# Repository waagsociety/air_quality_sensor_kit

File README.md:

# Air quality sensor kit
This repo contains documentation, source files and code for the following air quality sensor kits:

- Bora kit
- Bora Lora kit
- rIoT
- Responsive bird

### Bora kit
Air Quality Sensor for the Amsterdam Smart Citizens Lab, measures NO2, dust, temperature and humidity. Developed for a pilot in 2016 to measure air quality around the Valkenburgerstraat and Weesperstraat, under the name [Urban AirQ](http://waag.org/en/project/urban-airq). Citizens actively participated in the measuring process.

### Bora lora kit
The Bora kit was further developed during the [Smart Kids Lab](https://waag.org/en/blog/smart-citizen-kit-measuring-children-school) pilot to improve some criticalities with [LoraWAN](https://www.lora-alliance.org/What-IsLoRa/Technology):
- unstable and weak connectivity of the wifi module
- high power consumption,
- lack of real time data visualization.

### rIot
TBA

##### Credits
Partners: KNMI, University of Wageningen, GGD Amsterdam, ECN and the LongFonds. Waag Society earlier conducted a pilot with the Smart Citizen Kit in Amsterdam to measure air quality.

Partly financed by the Amsterdam Institute for Advanced Metropolitan Solutions (AMS). The project is also part of the European financed program Making Sense. This project has received funding from the European Union’s Horizon 2020 research and innovation programme under grant agreement no. 688620.

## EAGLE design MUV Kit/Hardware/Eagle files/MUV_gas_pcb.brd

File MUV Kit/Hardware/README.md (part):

If you are planning to produce the boards in the fablab you are in the right place. On this page you find instructions that will guide you during the process.
If you want to save time (and budget) you can download and use the gerber files of the customised boards from [folder](https://github.com/waagsociety/air_quality_sensor_kit/tree/master/MUV%20Kit/Hardware/Gerber%20files).

## Fab pcbs

The Fab boards are made using the small milling machine Roland Modela MDX-20, each pcbs requires at least two jobs: mill the trace and cut/drill the boards, in the folder digital files you find the png machinable files. When the pcb is double-side (the components and/or traces are on both side), the jobs are four: [double side milling](https://github.com/waagsociety/air_quality_sensor_kit/tree/master/MUV%20Kit/Hardware/Double%20side%20milling).

Tools used:
- one side and double side copper plate, FR1
- to mill the traces: endmill, 1/64inch diameter
- to cut and drill: endmill, 1/32inch diameter

In Fablab Amsterdam the software to generate the rml file and send it to the machine is Fabmodules. It is highly recommended to use the last version of Fabmodules, aka mods http://mods.cba.mit.edu/; previous versions of fabmodules, still work but double check the output of the software before to send the job to the machine, in some cases the path is not well calculated.

In the image below you find the setting to envrage the traces and to drill holes/cut the board.
<br>

Note: when you mill the outlines, you will need to trick the fabmodules!! Some holes are two smalls to be identified with a diameter tool of 1/64inch (0.79248mm) so you can set the diameter tool to 0.78mm and all the holes will be milled; yes, you lose some copper on the pad but it is still enough to solder vias and components.

#### Sensors pcb
| top view  | bottom view |
| ------------- | ------------- |
| |  |
| Components placed on the top layer  <br> but soldered on the bottom! <br>  <br> JP1: female THT 1x12 pin header, 2.54pitch <br> JP2: female THT 1x16 pin header 2.54pitch <br> J-GAS, J-DB. J-BME : Grove - Universal 4 Pin connector <br> 05-JST-B5B: Connector Wire-To-Board, B5B-XH-A (LF)(SN) <br> red traces: jumper wires between vias| Components placed on the bottom layer <br> and soldered on the bottom side <br>  <br> Q1/Q2 : BSS138 mosfet, also the NDS355AN from the fab inventory is ok. <br> R1/R2/R3/R4 : 10 Kohm <br> D1/D2 : diodes <br><br><br><br>|
|   | |

On the sensors pcb, it is not necessary to use all the connectors.
Depending on the sensors you want you use you can solder the required sockets. The J-GAS-NO1 and J-GAS-NO2 are dedicated to the Alphasense gas input devices. In this repo we are using only one sensor, the NO2 detector and it is connected to J-GAS-NO1.

#### Interface pcb
| top view  | bottom view |
| ------------- | ------------- |
|  | |
|Components placed on the top layer <br>   <br> SW_RST, SW_CONFIG: push button, smd, 6mm <br> LED1: WS2812B smd <br> R1: 10K res, smd, 1206 <br> R2: 470 ohm res, smd, 1206 <br> C1: 0.1uF cap, smd, 1206| Components placed on the bottom layer <br>  <br> JP3: female THT 1x12 pin header, 2.54pitch <br> JP1: female THT 1x16 pin header 2.54pitch <br><br><br><br>|

#### Temp/Hum pcb
| top view  | bottom view |
| ------------- | ------------- |
|   | |
| Components placed on the top layer <br>   <br> J3: female THT 1x6 pin header, 2.54pitch| Components placed on the bottom layer <br>  <br> J1: Grove - Universal 4 Pin connector|

The temp/hum pcb is a 2 layers board, the vias can be filled in with solid core wire (diameter < 0.8 mm). More information about the production of a double side pcb are in the [Double side milling](https://github.com/waagsociety/air_quality_sensor_kit/tree/master/MUV%20Kit/Hardware/Double%20side%20milling) section.

#### Gas pcb
| top view  | bottom view |
| ------------- | ------------- |
|   | |
| Components placed on the top layer <br>   <br> J2: Grove - Universal 4 Pin connector <br> JP1: female THT 1x10 pin header, 2.54pitch <br><br>| Components placed on the bottom layer <br>  <br> R1 or R2: 0 ohm resistor, smd, 1206 <br> C1: 100nF capacitor, smd, 1206 <br> C2: 1uF capacitor, smd, 1206 |

Note: this board can be used for both NO2 and O3 sensor but it is necessary to solder the zero ohm resistor in the different places depending on the gas. For the NO2 sensor the zero ohm resistor must be placed on R1, for the O3 sensor the zero ohm resistor must be placed on R2.

#### Noise pcb
| top view  | bottom view |
| ------------- | ------------- |
|   | |
| Components placed on the top layer <br>  <br> J1: Grove - Universal 4 Pin connector <br> OTS1_short: female THT 1x12 pin header, 2.54pitch <br> OTS1_long: female THT 1x16 pin header, 2.54pitch | There are no components placed on the bottom layer <br>  <br><br><br><br>|

## Off-the-shelf pcbs

#### Adafruit Feather esp8266
The [Adafruit Feather HUZZAH ESP8266](https://learn.adafruit.com/adafruit-feather-huzzah-esp8266?view=all) is an 'all-in-one' ESP8226 WiFi development board. The module can be supplied through USB cable with the following specifications:
* Measures 2.0" x 0.9" x 0.28" (51mm x 23mm x 8mm) without headers soldered in
* Light as a (large?) feather - 6 grams
* ESP8266 @ 80MHz or 160 Mhz with 3.3V logic/power
* 4MB of FLASH (32 Mbit)
* 3.3V regulator with 500mA peak current output
* CP2104 USB-Serial converter onboard with 921600 max baudrate for uploading
* Auto-reset support for getting into bootload mode before firmware upload
* 9 GPIO pins - can also be used as I2C and SPI
* 1 x analog inputs 1.0V max
* Pin #0 red LED for general purpose blinking. Pin #2 blue LED for bootloading debug & general purpose blinking
* Power/enable pin
* 4 mounting holes
* Reset button<br>

In this application the feather esp8266 is responsible to collect the measurements of the sensors and send them, via WiFi, to the dedicated server.
When the Wifi network is not available it can save the data on a SD-card, embedded on a different pcb, see section below.

The feather esp8266 requires female stacking headers so it can be plugged on the sensors pcb and it can host, on top, the RTC/SD-card pcb. The headers must be bought separately and they must be solder on the feather esp8266 board.

#### Adafruit Feather RTC and SD-card
The [Adalogger FeatherWing - RTC + SD](https://learn.adafruit.com/adafruit-adalogger-featherwing/overview) is compatible with the feather esp8266 and it features:
* an I2C real time clock (PCF8523) with 32KHz crystal and battery backup.
* microSD socket that connects to the SPI port pins. A CR1220 coin cell is required to use the RTC battery-backup capabilities.

As for the feather esp8266, it needs the female stacking headers that don't come with the board but they must be separately bought and soldered.

#### BME280 breakout board
The [bme280](https://www.bosch-sensortec.com/bst/products/all_products/bme280) sensor is so small (2.5x2.5 mm) that it is easier to work with its breakout board. The sensor works at 3.3V and it can communicate directly with the feather esp8266 that is also run at 3.3V, it means no need of level shifters between the two. Depending on where you buy the device, the board could already have the pin header, otherwise it is necessary to solder a 1x6 male header, 2.54mm pitch.

#### ADS1115 breakout board
The [ADS1115 board](https://learn.adafruit.com/adafruit-4-channel-adc-breakouts/) from Adafruit is the breakout board of the high-resolution Analog-to-Digital converter ADS1115. It is used in the reading of small voltages from the Gas sensors. The board can run from 2ßV up to 5V, in the kit it is supplied at 5V, same domain of the gas sensor, and it executes a two differential input readings.<br>
The [ADS1115](http://www.ti.com/lit/ds/symlink/ads1115.pdf) features:
* Resolution: 16 Bits
* Programmable Sample Rate: 8 to 860 Samples/Second
* Power Supply/Logic Levels: 2.0V to 5.5V
* Low Current Consumption: Continuous Mode: Only 150µA * Single-Shot Mode: Auto Shut-Down
* Internal Low-Drift Voltage Reference
* Internal Oscillator
* Internal PGA: up to x16
* I2C Interface: 4-Pin-Selectable Addresses
* Four Single-Ended or 2 Differential Inputs
* Programmable Comparator  

In the sensor kit, the ADS1115 board needs a 1x10 male pin header, pitch 2.54mm.

#### Adafruit Feather M0 Basic Proto
The Feather M0 Basic Proto has the ATSAMD21G18 ARM Cortex M0 processor as core, it clocked at 48MHz with 3,3V logic. Some specs:

* Measures 2.0" x 0.9" x 0.28" (51mm x 23mm x 8mm) without headers soldered in
* Light as a (large?) feather - 4.6 grams
* ATSAMD21G18 @ 48MHz with 3.3V logic/power
* 256KB of FLASH + 32KB of RAM
* 32.768 Khz crystal for clock generation & RTC
* 3.3V regulator with 500mA peak current output
* USB native support, comes with USB bootloader and * serial port debugging
* 20 GPIO pins
* Hardware Serial, hardware I2C, hardware SPI support
PWM outputs on all pins
* 6 x 12-bit analog inputs
* 1 x 10-bit analog output (DAC)
* Built in 100mA lipoly charger with charging status indicator LED, not in used in sensor kit.
* Pin #13 red LED for general purpose blinking
* Power/enable pin
* 4 mounting holes
* Reset button

In the kit the feather M0 is responsible to communicate with mic for the noise measurements and it sends the data to the feather esp8266 over serial.
The connect the fetaher M0 to pheripheral devices is necessary to solder:
* two 1x3 female pin headers on the proto part of the feather, as socket for the mic. See image below for connection.
* the pin headers: one 1x12 male pin and one 1x16 male pin header, both 2.54mm pitch.

As it is shown in the images below, the socket for the mic is connected to three GPIO pins of the feather M0.
It is handy to NOT solder the long on these three GPIO pads and keep the pads available for the wires of the mic.

<p align="center">  <br>
 </p>

#### ICS-43432 breakout board
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
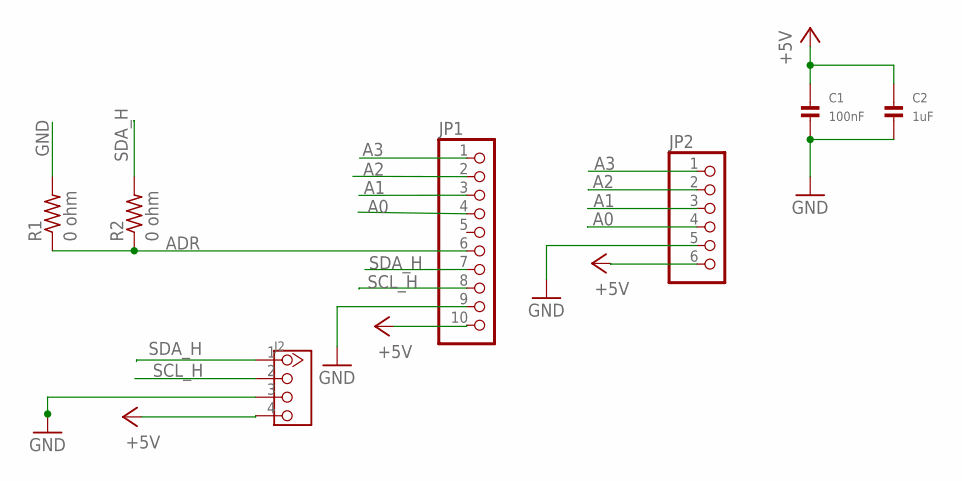
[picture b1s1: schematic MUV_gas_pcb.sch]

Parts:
C1: 100nF; 1206
C2: 1uF; 1206
J2: TWIG-4P-2.0-2.0; 4P-2.0
JP1: HEADER-1X10; 1X10_OVAL
JP2: HEADER-1X6; 1X06_OVAL
R1, R2: 0 ohm; 1206

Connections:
+5V: C1.1, C2.1, J2.4, JP1.10, JP2.6
A0: JP1.4, JP2.4
A1: JP1.3, JP2.3
A2: JP1.2, JP2.2
A3: JP1.1, JP2.1
ADR: JP1.6, R1.1, R2.1
GND: C1.2, C2.2, J2.3, JP1.9, JP2.5, R1.2
SCL_H: J2.2, JP1.8
SDA_H: J2.1, JP1.7, R2.2

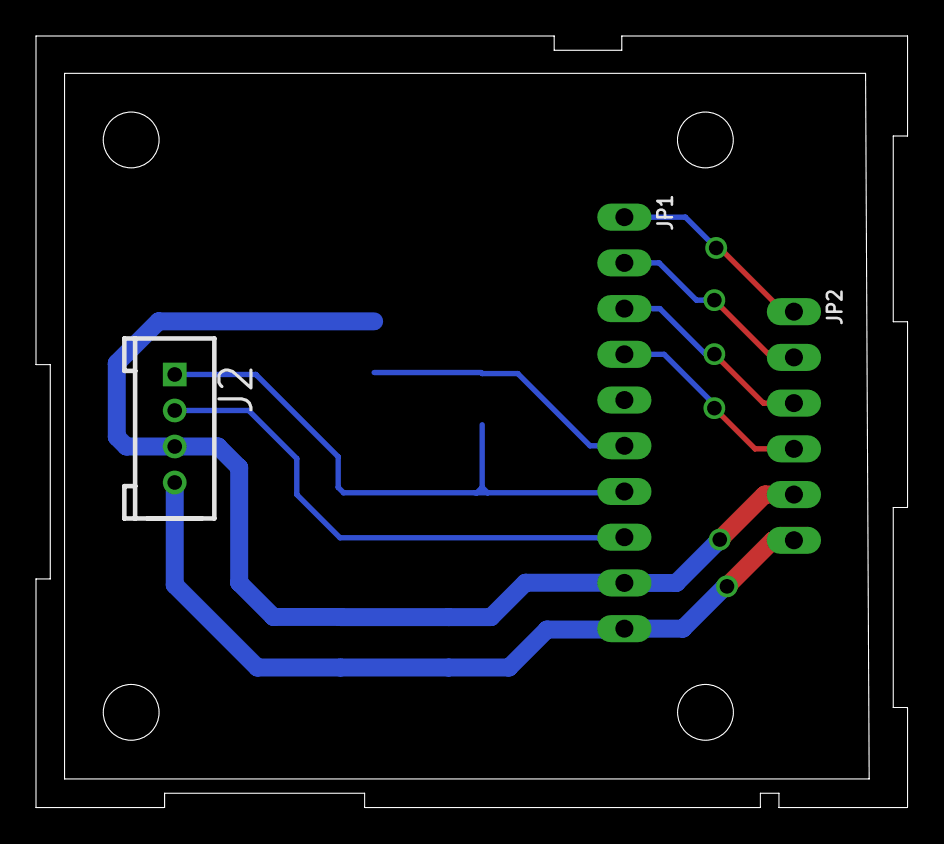
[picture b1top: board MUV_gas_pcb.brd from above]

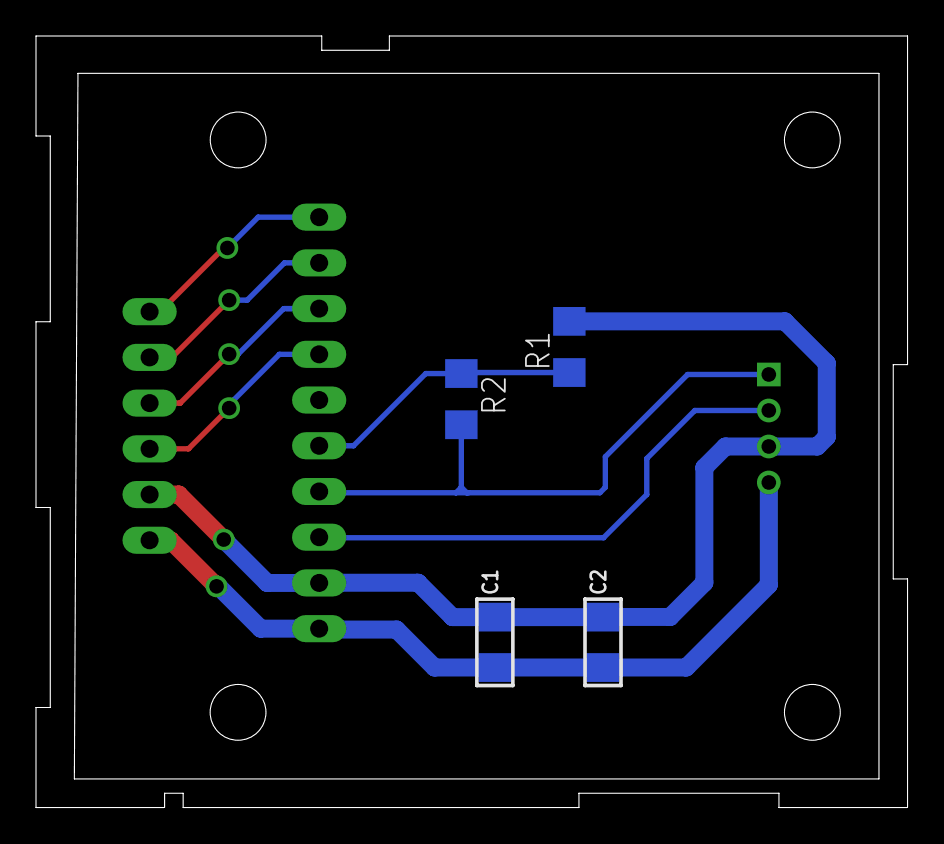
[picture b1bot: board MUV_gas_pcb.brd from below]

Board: 2 copper layers, 48.4 x 42.9 mm, 7 parts (4 on the bottom side), 9 nets.

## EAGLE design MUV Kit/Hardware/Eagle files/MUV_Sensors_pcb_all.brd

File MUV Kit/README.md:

# Air quality sensor kit for MUV

This repository is about the Sensors Kit developed for the project [MUV](https://www.muv2020.eu/) and contains the following parts:
- this page: you will find on this page the instructions on how it works.
- [Sensors](https://github.com/waagsociety/air_quality_sensor_kit/tree/master/MUV%20Kit/Sensors) folder: it contains the list of sensors that can be connected to the Kit.
- [Hardware](https://github.com/waagsociety/air_quality_sensor_kit/tree/master/MUV%20Kit/Hardware) folder: it contains digital files, original design files, layout view, instruction on how to produce the pcbs in a fablab, gerber files and BOM.
- [Firmware](https://github.com/waagsociety/air_quality_sensor_kit/tree/master/MUV%20Kit/Firmware) folder: it contains the sketches used in the Kit.
- [Case](https://github.com/waagsociety/air_quality_sensor_kit/tree/master/MUV%20Kit/Case) folder: it contains the instructions for the case.

## Intro
The MUV Sensors kit is a device developed to measure the following environmental quantities:
* dust (PM10 and PM2.5)
* temperature/humidity/pressure sensor
* nitrogen dioxide and ozone.

The kit has a WiFi module that collects the data from the sensors and send them to the MUV MQTT-server. If the WiFi is missing the kit saves the data on an SD-card.

NOTE: when you power on the kit, it must be able to connect to a WiFi otherwise it will not start the measurements.

Once the Kit is powered on and connected to the WiFi it will run automatically.

### Connect the Sensor Kit to the local WiFi
Power on the SK (Sensor Kit), plugging the USB cable. 
The kit will try to connect to the WiFi, during which the Led on the interface board will flash red. 
If no Wifi configuration is present, the kit wil enter configuration mode, indicated by a steady blue Led.

When in configuration mode, it creates a network named MUV_air.
At this point you need a smartphone/tablet or computer, join the network MUV_air.

If the Led keeps flashing red, you can enter configuration mode manually. Press and hold the 
SW_CONFIG button while pressing the SW_RST button. The kit should reset and start in
configuration mode with the blue Led on. Once the blue Led is on, you can release the SW_CONFIG
button.

Automatically on the device you are using (smartphone/tablet/computer) the configuration window will pop-up.

If the window doesn't appear, open a browser and go to the address: http://192.168.4.1/.

Clicking on Info, you can see the information related to the kit and find the kit ID that in the window is called Chip ID.
Clicking on Configure WiFi, you are in the right place to connect the kit to you local WiFi.

Select the WiFi and type the password.
In the tag "Insert address", write the location of the kit.

Click save and the kit will try to connect to the WiFi. The Led should flash red briefly, then turn green for a short time, then flash
magenta briefly and finally going off. The kit is now connected and starts the measurements.

** NOTE **
In case you want to change the location, you can enter configuration mode using the Config switch on the interface board: keep pushed the Config switch and reset the kit (press once the reset switch). Hold the Config switch until the Config Led turns blue.

### Explanation of the Led colors
- When you power the kit on, the Led blinks red while connecting to the WiFi. If it can't connect, it will continue to flash red.
- You can enter configuration mode as described above. When in configuration mode the Led is a steady blue.
- When the WiFi is connected succesfully, the Led is on green, while getting the current time from the NTP server and checking for a firmware update.
- Once the time is synchronised, the kit will attempt to connect to the MQTT server. During this the Led flashes magenta. If it can't connect
to the MQTT server, it will continue to flash magenta.
- Once the MQTT connection is made, the Led will go off and the measurements begin.
- Every time the data are pushed to the cloud, the Led blinks green if the uplink is successful. If the payload can't reach the server, the Led turns on/orange and the data are saved to the SD-card. If the kit is disconnected from the WiFi and can't save the data on the sd-card, the Led stays on/red.

### MUV

[*MUV*  Mobility Urban Values ](https://www.muv2020.eu) levers behavioural change in local communities using an innovative approach to improve urban mobility: changing citizens habits through a game that mixes digital and physical experiences.

Rather than focus on costly and rapidly ageing urban infrastructures, MUV promotes a shift towards more sustainable and healthy mobility choices by engaging in a positive way local communities, local businesses, policymakers and Open Data enthusiasts.

MUV solutions will be open, co-created with a strong learning community of users and stakeholders, and piloted in a set of diverse urban neighbourhoods spread across Europe: Amsterdam (NL), Barcelona (ES), Fundao (PT), Ghent (BE), Helsinki (FI), Palermo (IT).

Mobility and environmental data gathered via the mobile app and the monitoring stations will allow policymakers to enhance planning processes and civic hackers to build new services able to improve cities quality of life in a more effective way.

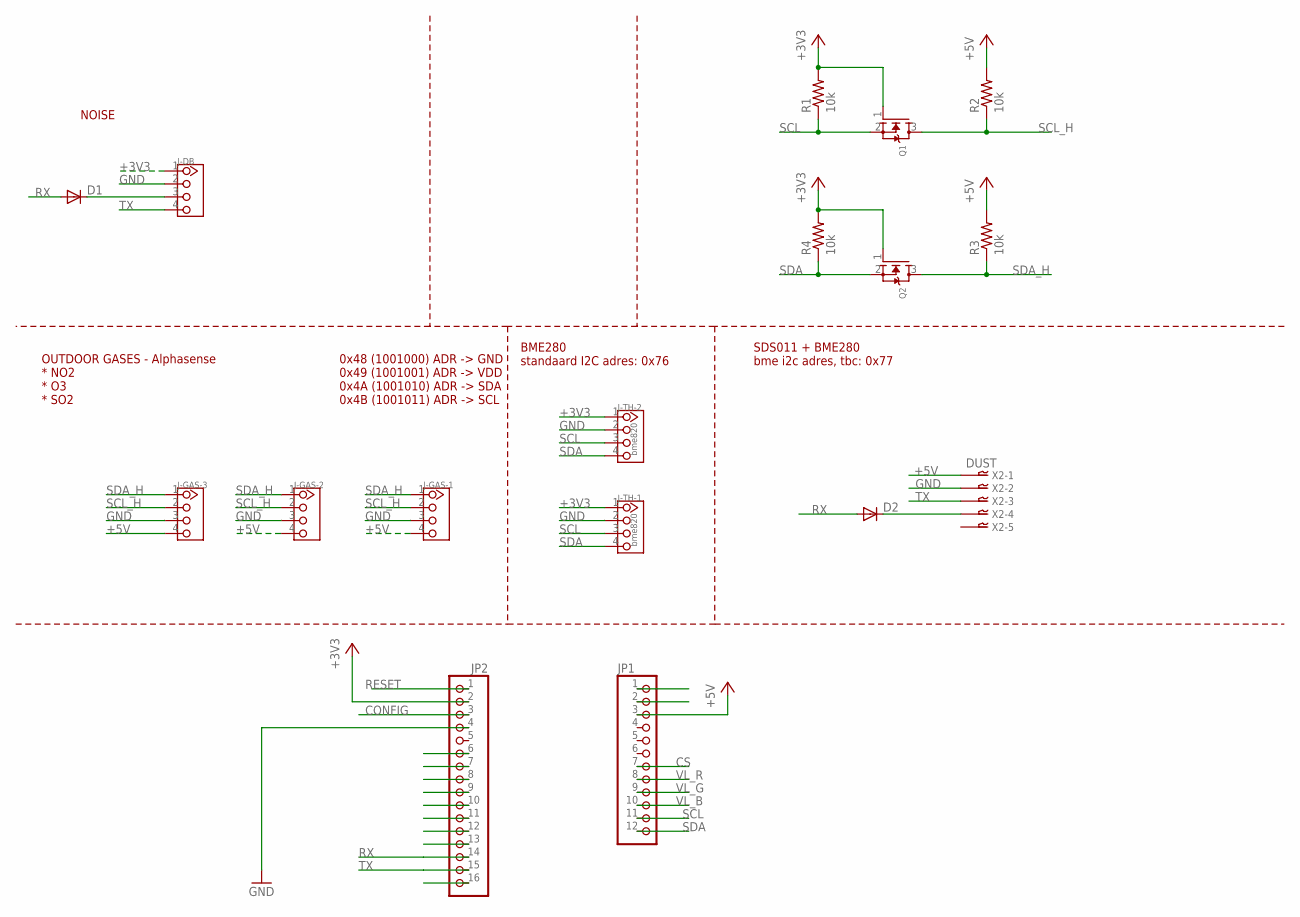
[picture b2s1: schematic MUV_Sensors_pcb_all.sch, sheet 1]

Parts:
D1, D2: DIODE-DO214AA; DO214AA
J-DB: TWIG-4P-2.0-2.0; 4P-2.0
J-GAS-1, J-GAS-2, J-GAS-3: TWIG-4P-2.0-2.0; 4P-2.0
J-TH-1, J-TH-2: bme820; 4P-2.0
JP1: HEADER-1X12OVAL; 1X12_OVAL
JP2: HEADER-1X16; 1X16_OVAL
Q1, Q2: MOSFET-NWIDE; SOT23-WIDE
R1, R2, R3, R4: 10k; 1206
X2: DUST; B5B-XH

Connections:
+3V3: J-DB.1, J-TH-1.1, J-TH-2.1, JP2.2, Q1.1 (G), Q2.1 (G), R1.2, R4.2
+5V: J-GAS-1.4, J-GAS-2.4, J-GAS-3.4, JP1.3, R2.2, R3.2, X2.P$1
CONFIG: JP2.3
CS: JP1.7
GND: J-DB.2, J-GAS-1.3, J-GAS-2.3, J-GAS-3.3, J-TH-1.2, J-TH-2.2, JP2.4, X2.P$2
unnamed: D1.C, J-DB.3
unnamed: D2.C, X2.P$4
RESET: JP2.1
RX: D1.A, D2.A, JP2.14
SCL: J-TH-1.3, J-TH-2.3, JP1.11, Q1.2 (S), R1.1
SCL_H: J-GAS-1.2, J-GAS-2.2, J-GAS-3.2, Q1.3 (D), R2.1
SDA: J-TH-1.4, J-TH-2.4, JP1.12, Q2.2 (S), R4.1
SDA_H: J-GAS-1.1, J-GAS-2.1, J-GAS-3.1, Q2.3 (D), R3.1
TX: J-DB.4, JP2.15, X2.P$3
VL_B: JP1.10
VL_G: JP1.9
VL_R: JP1.8

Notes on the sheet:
SDS011 + BME280 bme i2c adres, tbc: 0x77
BME280 standaard I2C adres: 0x76
OUTDOOR GASES - Alphasense * NO2 * O3 * SO2
0x48 (1001000) ADR -> GND 0x49 (1001001) ADR -> VDD 0x4A (1001010) ADR -> SDA 0x4B (1001011) ADR -> SCL
NOISE

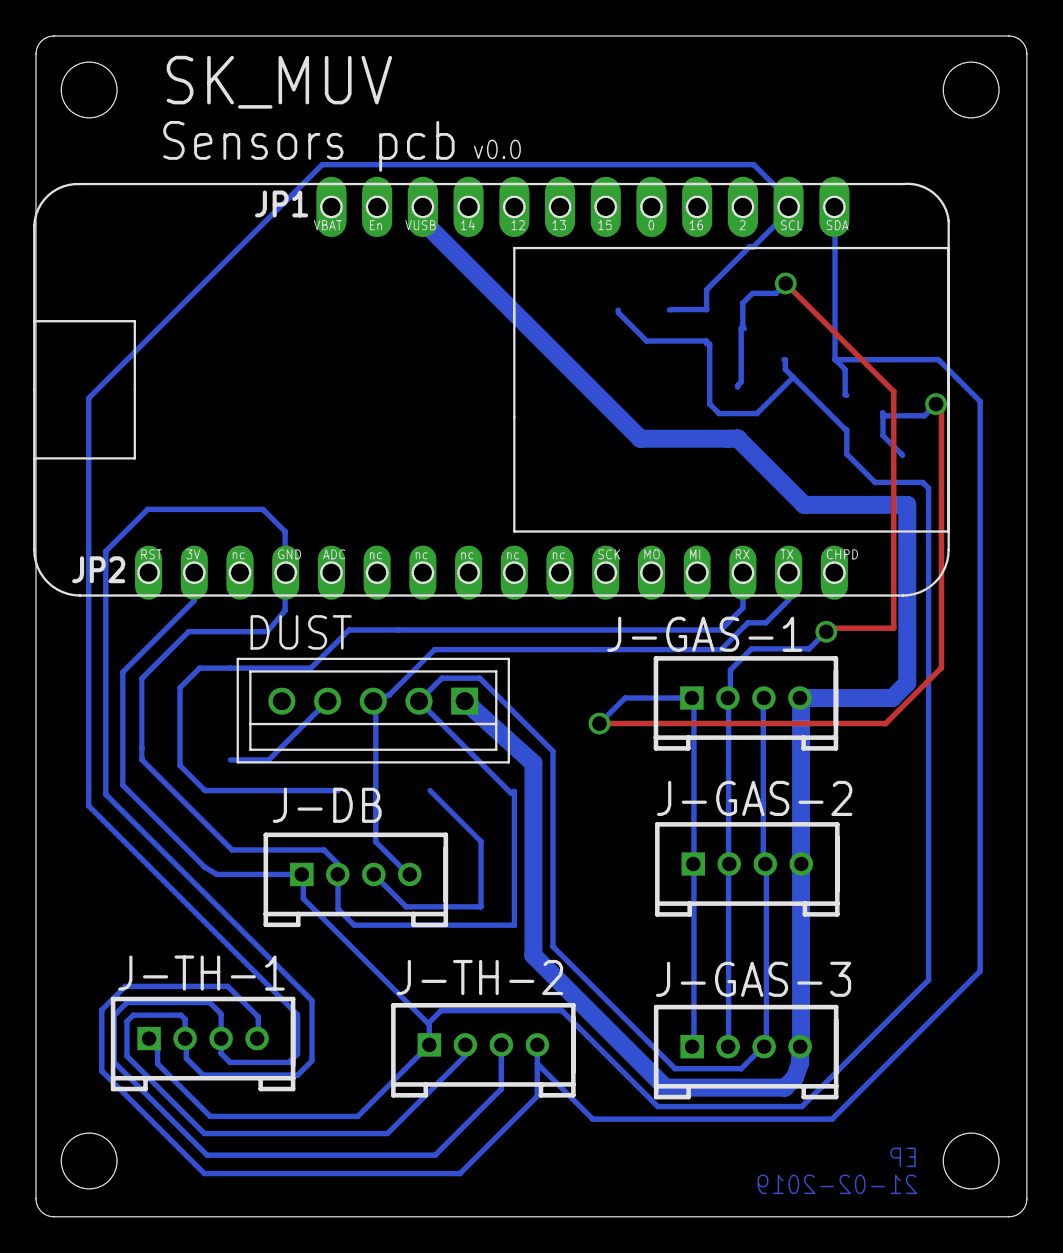
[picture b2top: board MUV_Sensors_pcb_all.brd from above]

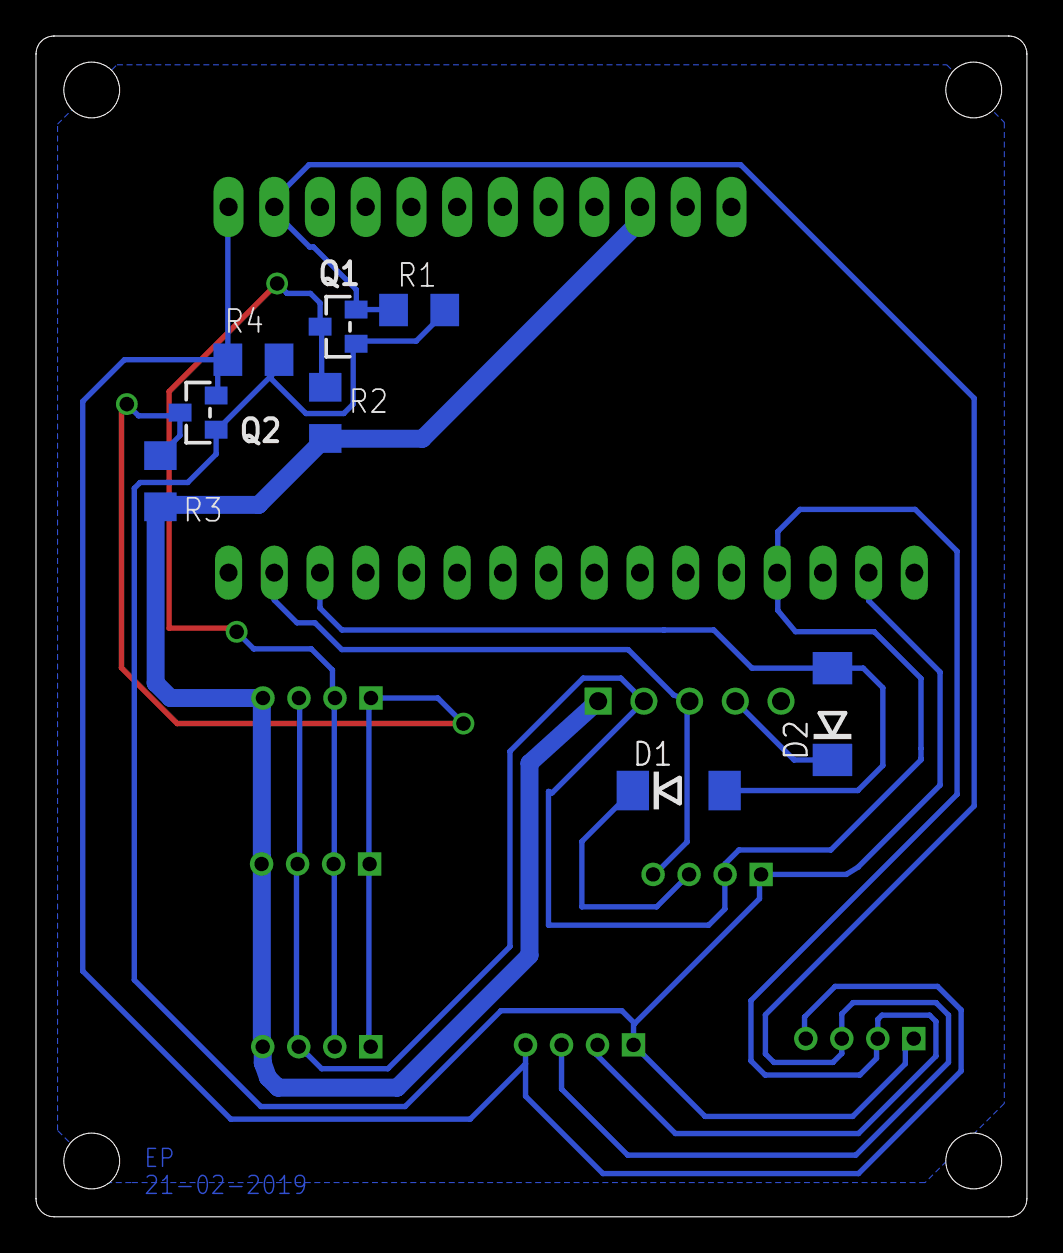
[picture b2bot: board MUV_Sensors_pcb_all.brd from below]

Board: 2 copper layers, 55.0 x 65.6 mm, 18 parts (8 on the bottom side), 11 nets.

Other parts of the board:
U1: ADA_FEATHER_HUZZAH_ESP8266_NOPADS

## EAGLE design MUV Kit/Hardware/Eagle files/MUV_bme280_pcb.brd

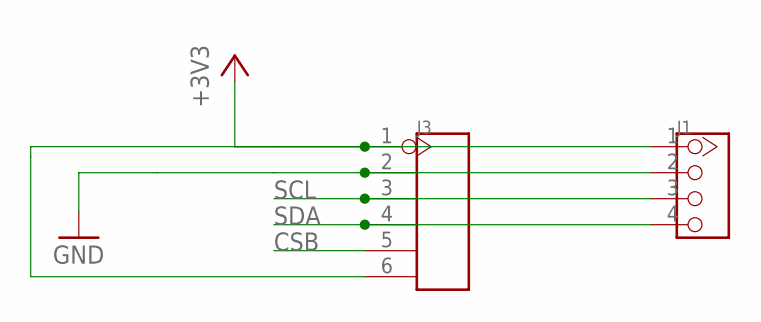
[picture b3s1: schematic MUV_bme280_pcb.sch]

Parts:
J1: TWIG-4P-2.0-2.0; 4P-2.0
J3: HEADER-6P-80/40MIL; 6P-2.54-80/40MIL

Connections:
+3V3: J1.1, J3.1, J3.6
CSB: J3.5
GND: J1.2, J3.2
SCL: J1.3, J3.3
SDA: J1.4, J3.4

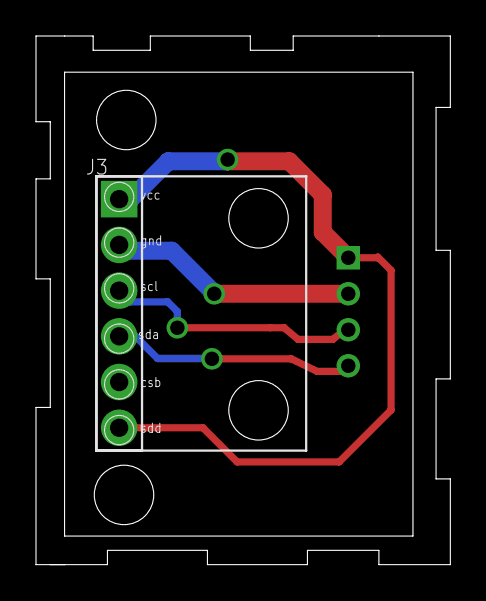
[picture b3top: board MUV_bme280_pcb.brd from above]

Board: 2 copper layers, 23.0 x 29.4 mm, 3 parts (1 on the bottom side), 4 nets.

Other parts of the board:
U$1: BME280_BO_NOPADS

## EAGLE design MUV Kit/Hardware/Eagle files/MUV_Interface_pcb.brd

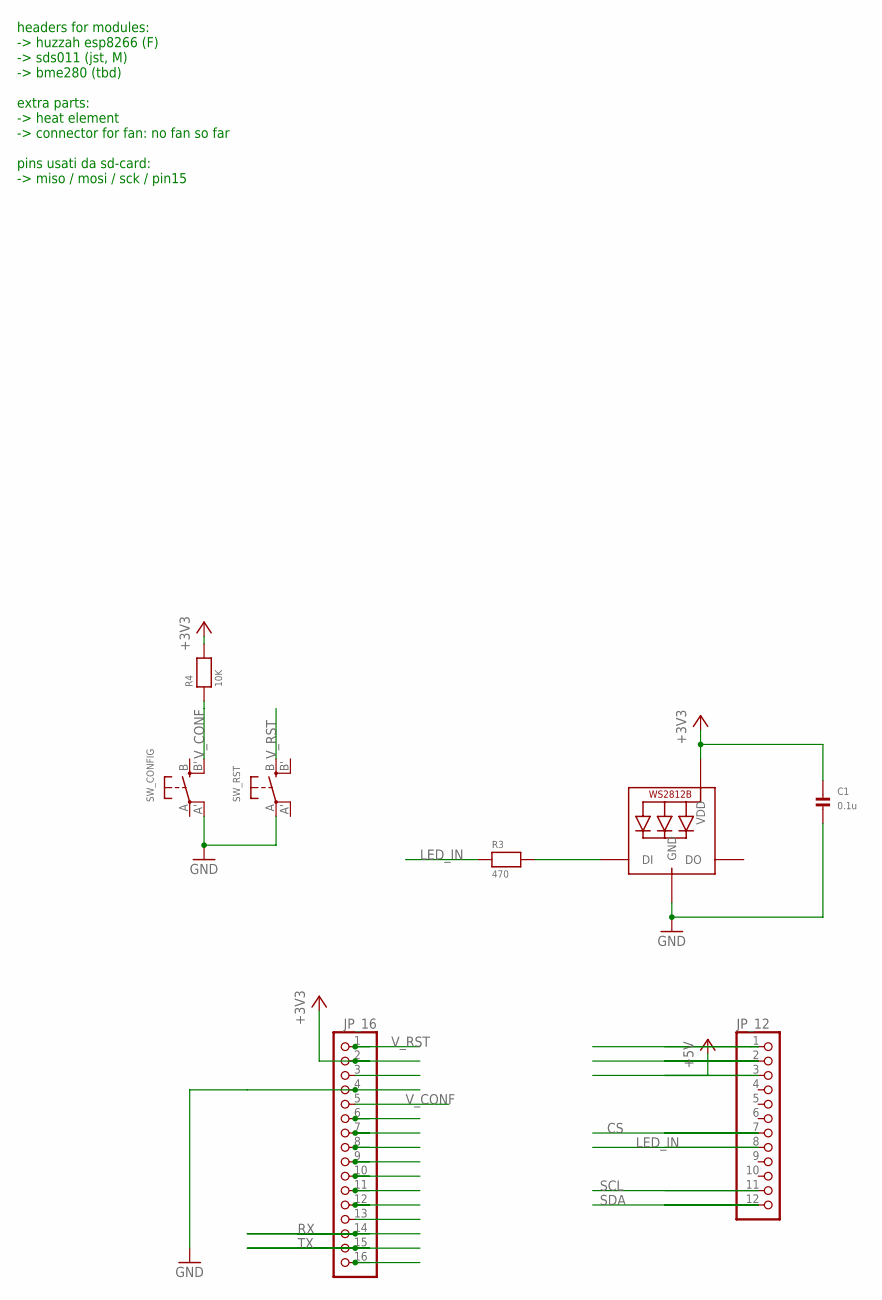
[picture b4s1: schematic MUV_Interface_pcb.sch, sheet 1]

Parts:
C1: 0.1u; 1206
JP_12: HEADER-1X12OVAL; 1X12_OVAL
JP_16: HEADER-1X16; 1X16_OVAL
LED1: WS2812B5050; WS2812B
R3: 470; 1206
R4: 10K; 1206
SW_CONFIG: SWITCH_TACT_SMT; EVQ-Q2
SW_RST: SWITCH_TACT_SMT; EVQ-Q2

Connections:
+3V3: C1.1, JP_16.2, LED1.1-VDD (VDD), R4.2
+5V: JP_12.3
CS: JP_12.7
GND: C1.2, JP_16.4, LED1.3-GND (GND), SW_CONFIG.A' (P1), SW_RST.A
LED_IN: JP_12.8, R3.1
unnamed: LED1.4-DIN (DI), R3.2
RX: JP_16.14
SCL: JP_12.11
SDA: JP_12.12
TX: JP_16.15
V_CONF: JP_16.5, R4.1, SW_CONFIG.B' (S1)
V_RST: JP_16.1, SW_RST.B (S)

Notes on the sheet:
headers for modules: -> huzzah esp8266 (F) -> sds011 (jst, M) -> bme280 (tbd) extra parts: -> heat element -> connector for fan: no fan so far pins usati da sd-card: -> miso / mosi / sck / pin15

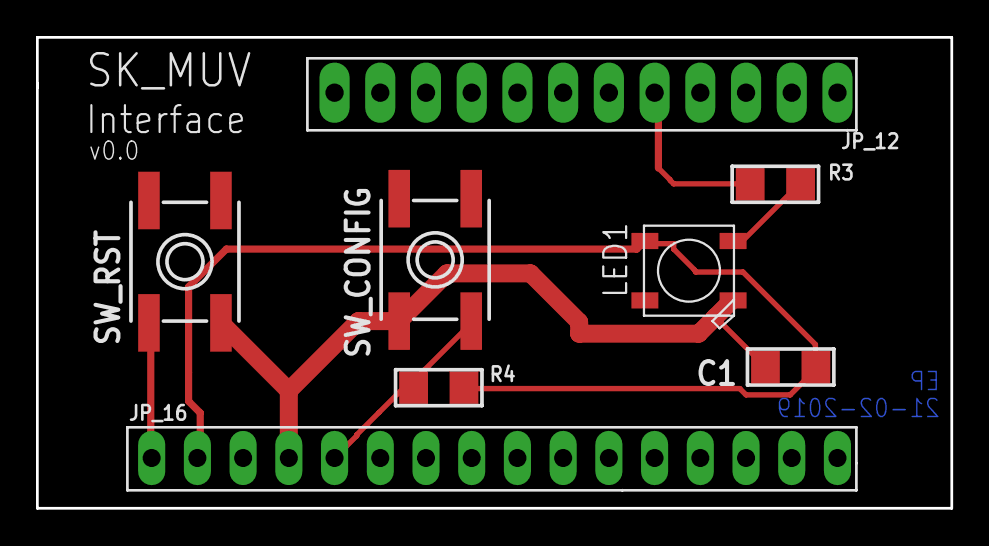
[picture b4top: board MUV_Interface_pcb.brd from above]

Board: 2 copper layers, 50.8 x 26.2 mm, 8 parts (0 on the bottom side), 6 nets.

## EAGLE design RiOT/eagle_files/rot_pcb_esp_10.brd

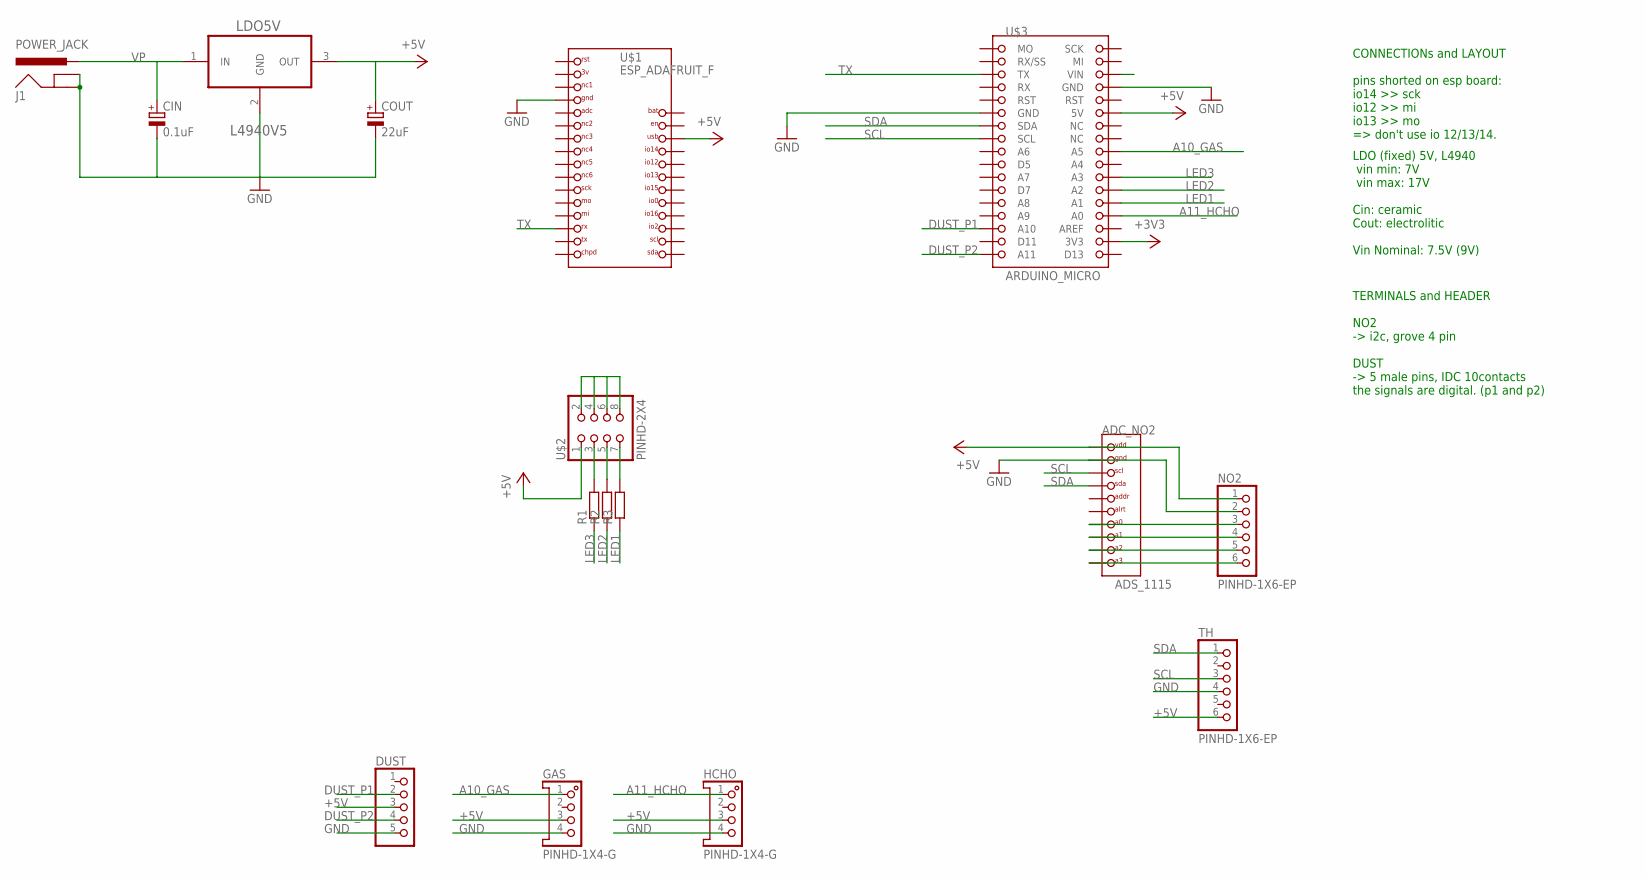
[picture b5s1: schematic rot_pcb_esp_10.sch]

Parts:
ADC_NO2: ADS_1115
CIN: 0.1uF; B45181B
COUT: 22uF; E2-5
DUST: PINHD-1X5; 1X5
GAS: PINHD-1X4-G; 1X4_G
HCHO: PINHD-1X4-G; 1X4_G
J1: POWER_JACK; POWER_JACK_PTH
LDO5V: L4940V5; TO254P482X1024X3124-3P
NO2: PINHD-1X6-EP; 1X6
R1, R2, R3: R-EU_0204/7; 0204/7
TH: PINHD-1X6-EP; 1X6
U$1: ESP_ADAFRUIT_F
U$2: PINHD-2X4; 2X4
U$3: ARDUINO_MICRO

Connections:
3V: U$1.3V
+3V3: U$3.3V3
+5V: ADC_NO2.VDD, COUT.+, DUST.3, GAS.3, HCHO.3, LDO5V.3 (OUT), NO2.1, TH.6, U$1.USB, U$2.1, U$3.5V
A4: U$3.A4
A10_GAS: GAS.1, U$3.A5
A11_HCHO: HCHO.1, U$3.A0
AREF: U$3.AREF
BAT: U$1.BAT
D13: U$3.D13
DUST_P1: DUST.2, U$3.A10
DUST_P2: DUST.4, U$3.A11
EN: U$1.EN
GND: ADC_NO2.GND, CIN.-, COUT.-, DUST.5, GAS.4, HCHO.4, J1.GND, J1.GNDBREAK, LDO5V.2 (GND), NO2.2, TH.4, U$1.GND, U$3.GND1 (GND), U$3.GND2 (GND)
LED1: R3.1, U$3.A1
LED2: R2.1, U$3.A2
LED3: R1.1, U$3.A3
MI: U$3.MI
unnamed: ADC_NO2.A3, NO2.6
unnamed: ADC_NO2.A2, NO2.5
unnamed: ADC_NO2.A1, NO2.4
unnamed: ADC_NO2.A0, NO2.3
unnamed: R1.2, U$2.3
unnamed: R2.2, U$2.5
unnamed: R3.2, U$2.7
unnamed: U$2.2, U$2.4, U$2.6, U$2.8
NC: U$3.NC1 (NC), U$3.NC2 (NC)
RST: U$3.RST2 (RST)
SCK: U$3.SCK
SCL: ADC_NO2.SCL, TH.3, U$3.SCL
SDA: ADC_NO2.SDA, TH.1, U$3.SDA
TX: U$1.RX, U$3.TX
VP: CIN.+, J1.PWR, LDO5V.1 (IN)

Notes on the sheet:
LDO (fixed) 5V, L4940 vin min: 7V vin max: 17V Cin: ceramic Cout: electrolitic Vin Nominal: 7.5V (9V)
CONNECTIONs and LAYOUT pins shorted on esp board: io14 >> sck io12 >> mi io13 >> mo => don't use io 12/13/14.
TERMINALS and HEADER NO2 -> i2c, grove 4 pin DUST -> 5 male pins, IDC 10contacts the signals are digital. (p1 and p2)

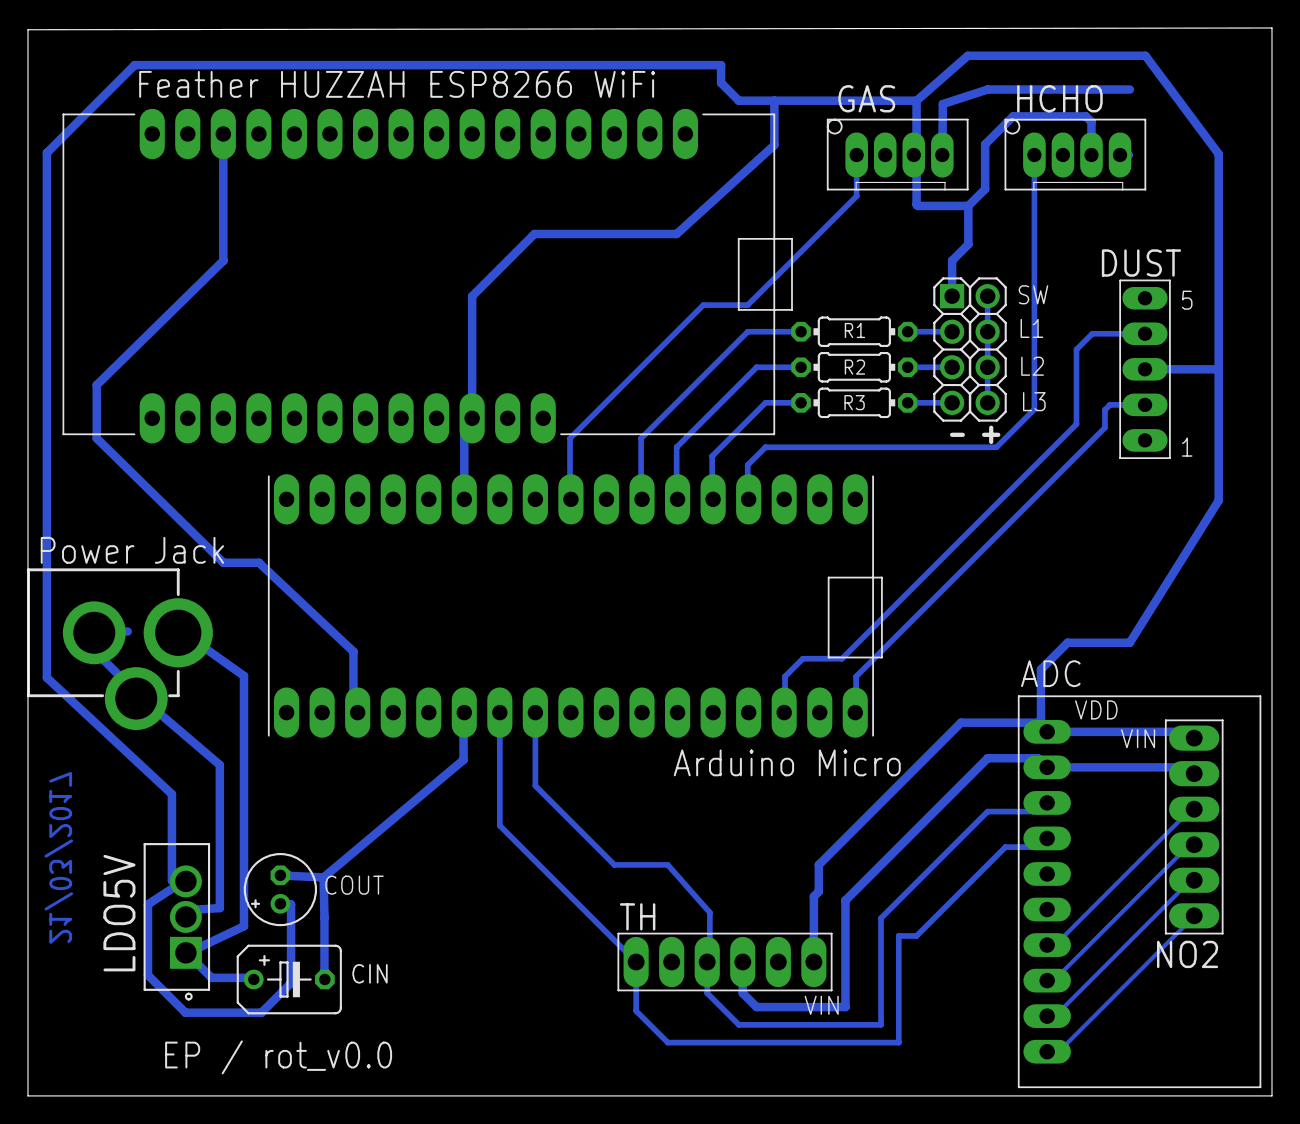
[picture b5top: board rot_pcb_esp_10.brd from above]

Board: 1 copper layer, 88.9 x 76.3 mm, 16 parts (0 on the bottom side), 22 nets.

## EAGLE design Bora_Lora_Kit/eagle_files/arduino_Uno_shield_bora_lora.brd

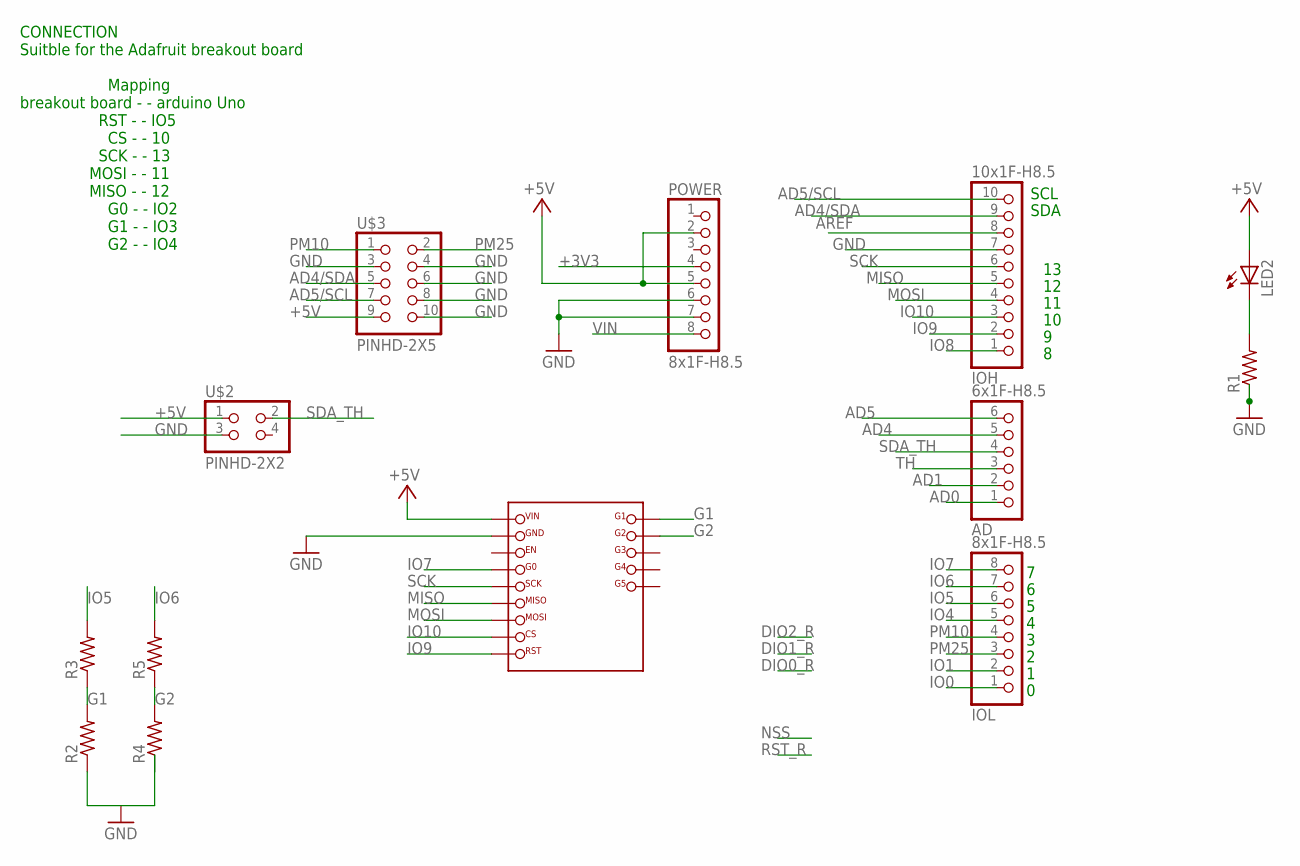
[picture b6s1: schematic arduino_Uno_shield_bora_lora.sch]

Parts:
AD: 6x1F-H8.5; 1X06
IOH: 10x1F-H8.5; 1X10
IOL: 8x1F-H8.5; 1X08
LED2: LED3MM
POWER: 8x1F-H8.5; 1X08
R1, R2, R3, R4, R5: RESISTOR1206; 1206
U$1: RFM95W_ADAFRUIT
U$2: PINHD-2X2; 2X2
U$3: PINHD-2X5; 2X5

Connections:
+3V3: POWER.4
+5V: LED2.A, POWER.2, POWER.5, U$1.VIN, U$2.1, U$3.9
AD0: AD.1
AD1: AD.2
AD4: AD.5
AD4/SDA: IOH.9, U$3.5
AD5: AD.6
AD5/SCL: IOH.10, U$3.7
AREF: IOH.8
G1: R2.2, R3.1, U$1.G1
G2: R4.2, R5.1, U$1.G2
GND: IOH.7, POWER.6, POWER.7, R1.1, R2.1, R4.1, U$1.GND, U$2.3, U$3.3, U$3.4, U$3.6, U$3.8, U$3.10
IO0: IOL.1
IO1: IOL.2
IO4: IOL.5
IO5: IOL.6, R3.2
IO6: IOL.7, R5.2
IO7: IOL.8, U$1.G0
IO8: IOH.1
IO9: IOH.2, U$1.RST
IO10: IOH.3, U$1.CS
MISO: IOH.5, U$1.MISO
MOSI: IOH.4, U$1.MOSI
unnamed: LED2.K (C), R1.2
PM10: IOL.4, U$3.1
PM25: IOL.3, U$3.2
SCK: IOH.6, U$1.SCK
SDA_TH: AD.4, U$2.2
TH: AD.3
VIN: POWER.8

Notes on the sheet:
SDA
SCL
CONNECTION Suitble for the Adafruit breakout board Mapping breakout board - - arduino Uno RST - - IO5 CS - - 10 SCK - - 13 MOSI - - 11 MISO - - 12 G0 - - IO2 G1 - - IO3 G2 - - IO4

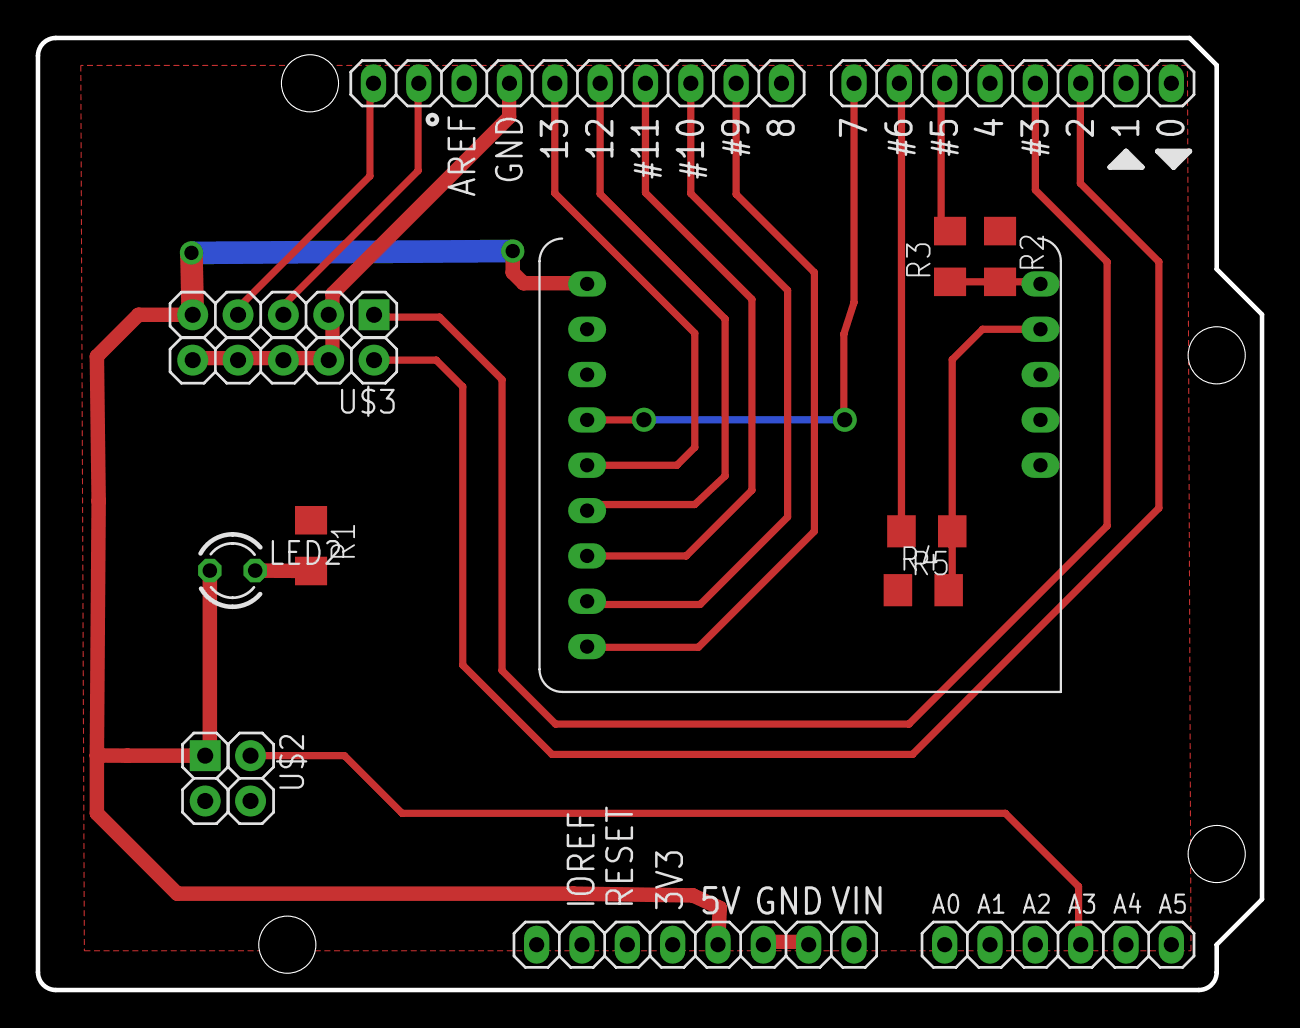
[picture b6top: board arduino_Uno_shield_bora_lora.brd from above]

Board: 2 copper layers, 68.6 x 53.3 mm, 13 parts (0 on the bottom side), 18 nets.

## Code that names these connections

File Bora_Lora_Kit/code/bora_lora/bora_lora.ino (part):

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float countP1;
float countP2;

#define DUST_P1_PIN 3      // Dust sensor PM2.5 pin
#define DUST_P2_PIN 2      // Dust senspr PM10 pin


//---------------------------
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  // take samples for 30 seconds
  while ((millis() - starttime) < sampletime_ms) {
 
    valP1 = digitalRead(DUST_P1_PIN); // 3
    valP2 = digitalRead(DUST_P2_PIN);  // 2
  
    if (valP1 == LOW && triggerP1 == false) {
      triggerP1 = true;
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  pinMode(DHTPIN, INPUT);
  dht.begin();

  pinMode(DUST_P1_PIN, INPUT); 
  pinMode(DUST_P2_PIN, INPUT); 
    
  Serial.begin(115200);
  Serial.println(F("Starting"));
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
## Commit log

2017-05-30 add index
2017-05-30 add intro
2017-05-30 add learn
2017-05-30 add sensor kit
2017-05-30 fix consumption table in sensor kit
2017-06-01 change repo name
2017-06-01 add Bora Lora as subfolder
2017-06-01 readme
2017-06-01 add .ino
2017-06-01 add eagle_file
2017-06-01 organize the repo
2017-06-01 add Bora Kit folder
2017-06-01 add rivm eagle files
2017-06-06 add data and conclusio
2017-07-03 update text
2017-07-03 upload presentation
2018-06-14 Create pic
2018-12-17 test
2018-12-18 machinable files
2018-12-18 .DS_Store banished!
2018-12-18 readme hardware
2018-12-19 hardware
2019-01-09 upload bom
2019-01-23 add codes
2019-01-23 fix wrong code for M0
2019-01-23 update firmware
2019-01-23 update firmware page
2019-01-24 sensors page
2019-01-24 main page
2019-02-13 update BOM
2019-02-14 update sensors pcb
2019-02-19 Add Case folder to instructions
2019-02-19 Adding instruction file
2019-02-19 Remove pdf file since it is incomplete
2019-02-19 Add pictures of the steps
2019-02-25 order of washers
2019-02-27 Updating links
2019-02-27 Updating pictures and BOM, plus one more laser cut file
2019-03-13 eagle for MUV
2019-03-18 png L1
2019-03-19 update hardware page
2019-03-19 clean double text
2019-03-20 update sds cable
2019-03-21 gerber files
2019-03-21 fix link
2019-03-22 update 6way conn BOM
2019-04-04 fix list
2019-05-03 add MUV_ESP8266_format.ino
2019-10-17 MUV files
2019-10-17 logo credits
2019-10-17 images
2019-10-28 New 2.0-7 firmware version for the MUV Monitoring Station. Changes: - Wifi connection more stable, no timeout - Over the air firmware update - Real time clock sync with Network Time in UTC - Better d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
2019-10-28 small fix to firmware/Readme.mg
2019-10-29 edit of formware/readme.md. changed firmware path in config.json

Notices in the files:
Bora_Lora_Kit/code/bora_lora/bora_lora.ino:
Copyright (c) <2017> <Emma Pareschi>
Bora_Lora_Kit/eagle_files/arduino_Uno_shield_bora_lora.brd:
Released under the Creative Commons Attribution Share-Alike 4.0 Licence
https://creativecommons.org/licenses/by-sa/4.0
parts and their libraries:
microbuilder: This work is placed in the public domain, and may be freely used for commercial and non-commercial work with the following conditions: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
